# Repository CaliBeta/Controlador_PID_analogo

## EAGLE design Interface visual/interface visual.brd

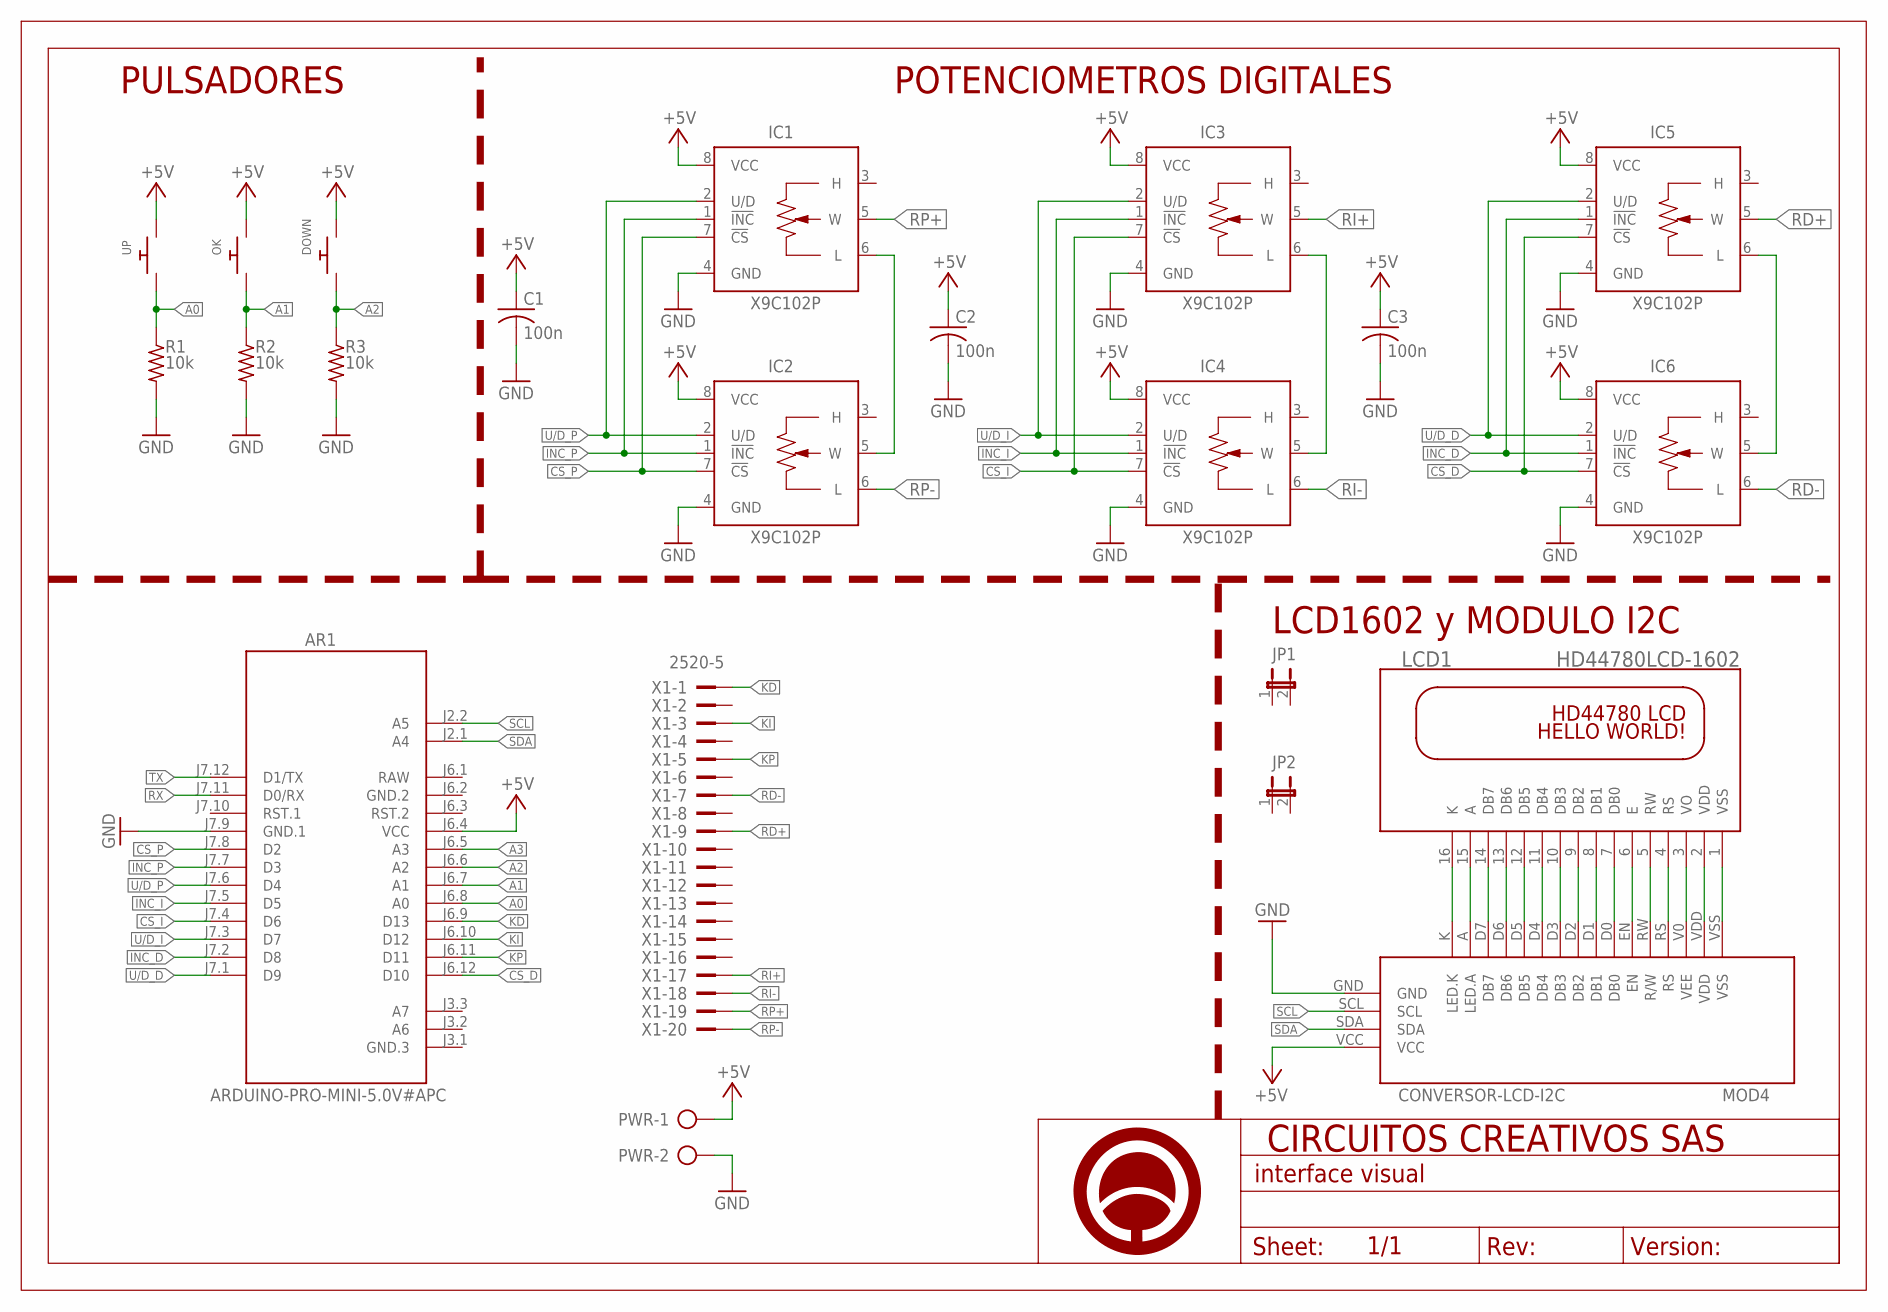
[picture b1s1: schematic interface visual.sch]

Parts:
AR1: ARDUINO-PRO-MINI-5.0V#APC; ARDUINO-PRO-MINI#APC
C1, C2, C3: 100n; C025-025X050
DOWN: SWITCH_PUSHBUTTONEVQ-PE; TACT_PANA-EVQ
IC1, IC2, IC3, IC4, IC5, IC6: X9C102P; DIL08
JP1, JP2: JP1E; JP1
LCD1: HD44780LCD-1602; LCD1602
MOD4: CONVERSOR-LCD-I2C
OK: SWITCH_PUSHBUTTONEVQ-PE; TACT_PANA-EVQ
PWR: AK500/2
R1, R2, R3: 10k; 0204/7
U$1: A4_HORIZONTAL; LOGO
UP: SWITCH_PUSHBUTTONEVQ-PE; TACT_PANA-EVQ
X1: 2520-5; PAK100/2500-5-20

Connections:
+5V: AR1.J6.4 (VCC), C1.1, C2.1, C3.1, DOWN.P$2, IC1.8 (VCC), IC2.8 (VCC), IC3.8 (VCC), IC4.8 (VCC), IC5.8 (VCC), IC6.8 (VCC), MOD4.VCC, OK.P$2, PWR.1, UP.P$2
A0: AR1.J6.8 (A0), R1.1, UP.P$1
A1: AR1.J6.7 (A1), OK.P$1, R2.1
A2: AR1.J6.6 (A2), DOWN.P$1, R3.1
A3: AR1.J6.5 (A3)
CS_D: AR1.J6.12 (D10), IC5.7 (!CS), IC6.7 (!CS)
CS_I: AR1.J7.4 (D6), IC3.7 (!CS), IC4.7 (!CS)
CS_P: AR1.J7.8 (D2), IC1.7 (!CS), IC2.7 (!CS)
GND: AR1.J7.9 (GND.1), C1.2, C2.2, C3.2, IC1.4 (GND), IC2.4 (GND), IC3.4 (GND), IC4.4 (GND), IC5.4 (GND), IC6.4 (GND), MOD4.GND, PWR.2, R1.2, R2.2, R3.2
GND.2: AR1.J6.2 (GND.2)
INC_D: AR1.J7.2 (D8), IC5.1 (!INC), IC6.1 (!INC)
INC_I: AR1.J7.5 (D5), IC3.1 (!INC), IC4.1 (!INC)
INC_P: AR1.J7.7 (D3), IC1.1 (!INC), IC2.1 (!INC)
KD: AR1.J6.9 (D13), X1.1
KI: AR1.J6.10 (D12), X1.3
KP: AR1.J6.11 (D11), X1.5
unnamed: IC3.6 (L), IC4.5 (W)
unnamed: IC1.6 (L), IC2.5 (W)
unnamed: IC5.6 (L), IC6.5 (W)
unnamed: LCD1.3 (VO), MOD4.V0 (VEE)
unnamed: LCD1.4 (RS), MOD4.RS
unnamed: LCD1.5 (RW), MOD4.RW (R/W)
unnamed: LCD1.7 (DB0), MOD4.D0 (DB0)
unnamed: LCD1.6 (E), MOD4.EN
unnamed: LCD1.8 (DB1), MOD4.D1 (DB1)
unnamed: LCD1.9 (DB2), MOD4.D2 (DB2)
unnamed: LCD1.10 (DB3), MOD4.D3 (DB3)
unnamed: LCD1.11 (DB4), MOD4.D4 (DB4)
unnamed: LCD1.12 (DB5), MOD4.D5 (DB5)
unnamed: LCD1.13 (DB6), MOD4.D6 (DB6)
unnamed: LCD1.14 (DB7), MOD4.D7 (DB7)
unnamed: LCD1.15 (A), MOD4.A (LED.A)
unnamed: LCD1.16 (K), MOD4.K (LED.K)
RAW: AR1.J6.1 (RAW)
RD+: IC5.5 (W), X1.9
RD-: IC6.6 (L), X1.7
RI+: IC3.5 (W), X1.17
RI-: IC4.6 (L), X1.18
RP+: IC1.5 (W), X1.19
RP-: IC2.6 (L), X1.20
RX: AR1.J7.11 (D0/RX)
SCL: AR1.J2.2 (A5), MOD4.SCL
SDA: AR1.J2.1 (A4), MOD4.SDA
TX: AR1.J7.12 (D1/TX)
U/D_D: AR1.J7.1 (D9), IC5.2 (U/D), IC6.2 (U/D)
U/D_I: AR1.J7.3 (D7), IC3.2 (U/D), IC4.2 (U/D)
U/D_P: AR1.J7.6 (D4), IC1.2 (U/D), IC2.2 (U/D)
VDD: LCD1.2 (VDD), MOD4.VDD
VSS: LCD1.1 (VSS), MOD4.VSS

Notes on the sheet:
LCD1602 y MODULO I2C
POTENCIOMETROS DIGITALES
PULSADORES

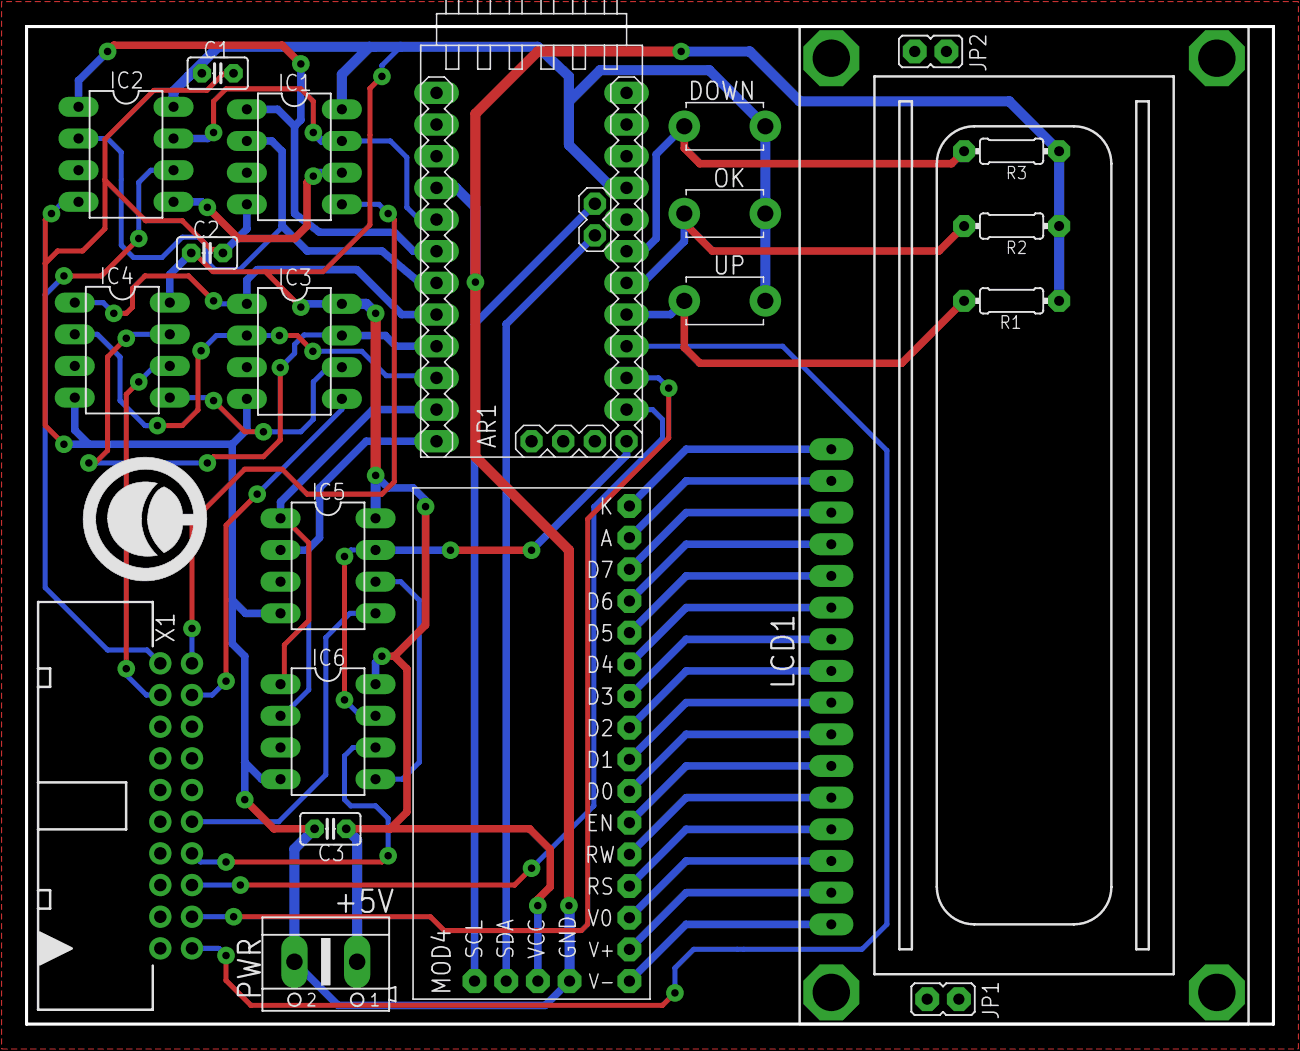
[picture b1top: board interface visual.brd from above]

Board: 2 copper layers, 100.0 x 80.0 mm, 23 parts (0 on the bottom side), 44 nets.

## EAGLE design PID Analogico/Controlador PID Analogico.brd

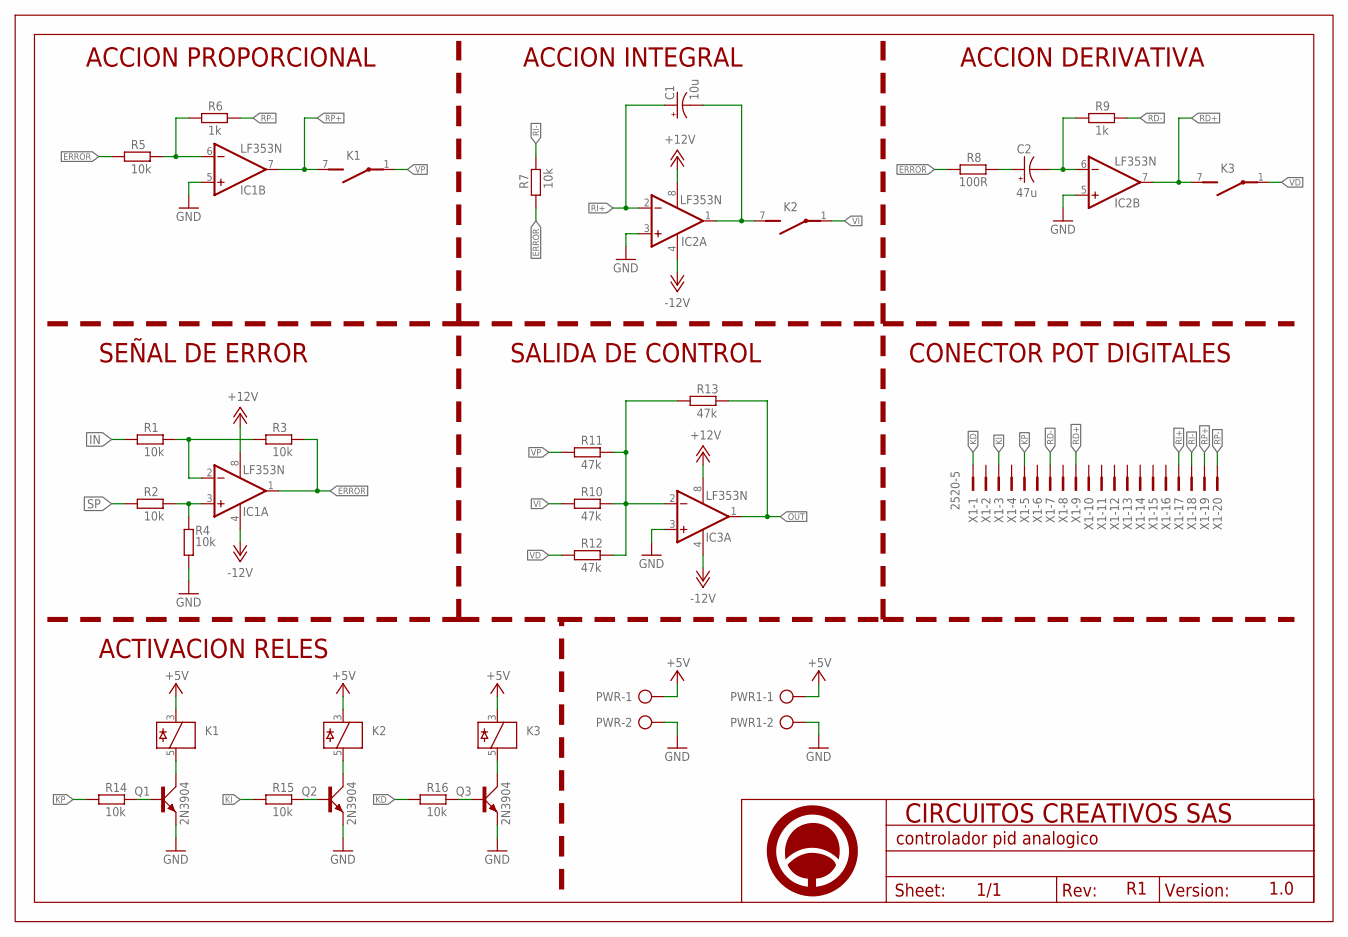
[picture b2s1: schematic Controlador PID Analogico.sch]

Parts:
C1: 10u; E2,5-6E
C2: 47u; E2,5-6E
IC1, IC2, IC3: LF353N; DIL08
K1, K2, K3: 35701331; REED
PWR, PWR1: AK500/2
Q1, Q2, Q3: 2N3904; TO92D
R1, R2, R3, R4, R5, R7, R14, R15, R16: 10k; 0204/7
R6, R9: 1k; 0204/7
R8: 100R; 0204/7
R10, R11, R12, R13: 47k; 0204/7
U$1: A4_HORIZONTAL; LOGO
X1: 2520-5; PAK100/2500-5-20

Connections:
+5V: K1.3, K2.3, K3.3, PWR.1, PWR1.1
+12V: IC1.8 (V+), IC2.8 (V+), IC3.8 (V+)
-12V: IC1.4 (V-), IC2.4 (V-), IC3.4 (V-)
ERROR: IC1.1 (OUT), R3.2, R5.2, R7.2, R8.1
GND: IC1.5 (+IN), IC2.3 (+IN), IC2.5 (+IN), IC3.3 (+IN), PWR.2, PWR1.2, Q1.E, Q2.E, Q3.E, R4.2
IN: R1.1
KD: R16.1, X1.1
KI: R15.1, X1.3
KP: R14.1, X1.5
unnamed: IC1.2 (-IN), R1.2, R3.1
unnamed: IC1.3 (+IN), R2.2, R4.1
unnamed: IC1.6 (-IN), R5.1, R6.1
unnamed: C1.-, IC2.1 (OUT), K2.7 (S)
unnamed: C2.-, IC2.6 (-IN), R9.1
unnamed: C2.+, R8.2
unnamed: IC3.2 (-IN), R10.2, R11.2, R12.2, R13.1
unnamed: Q1.B, R14.2
unnamed: K1.5, Q1.C
unnamed: Q2.B, R15.2
unnamed: K2.5, Q2.C
unnamed: Q3.B, R16.2
unnamed: K3.5, Q3.C
OUT: IC3.1 (OUT), R13.2
RD+: IC2.7 (OUT), K3.7 (S), X1.9
RD-: R9.2, X1.7
RI+: C1.+, IC2.2 (-IN), X1.17
RI-: R7.1, X1.18
RP+: IC1.7 (OUT), K1.7 (S), X1.19
RP-: R6.2, X1.20
SP: R2.1
VD: K3.1, R12.1
VI: K2.1, R10.1
VP: K1.1, R11.1

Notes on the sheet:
1.0
ACCION PROPORCIONAL
ACCION INTEGRAL
ACCION DERIVATIVA
SEÑAL DE ERROR
SALIDA DE CONTROL
ACTIVACION RELES
CONECTOR POT DIGITALES

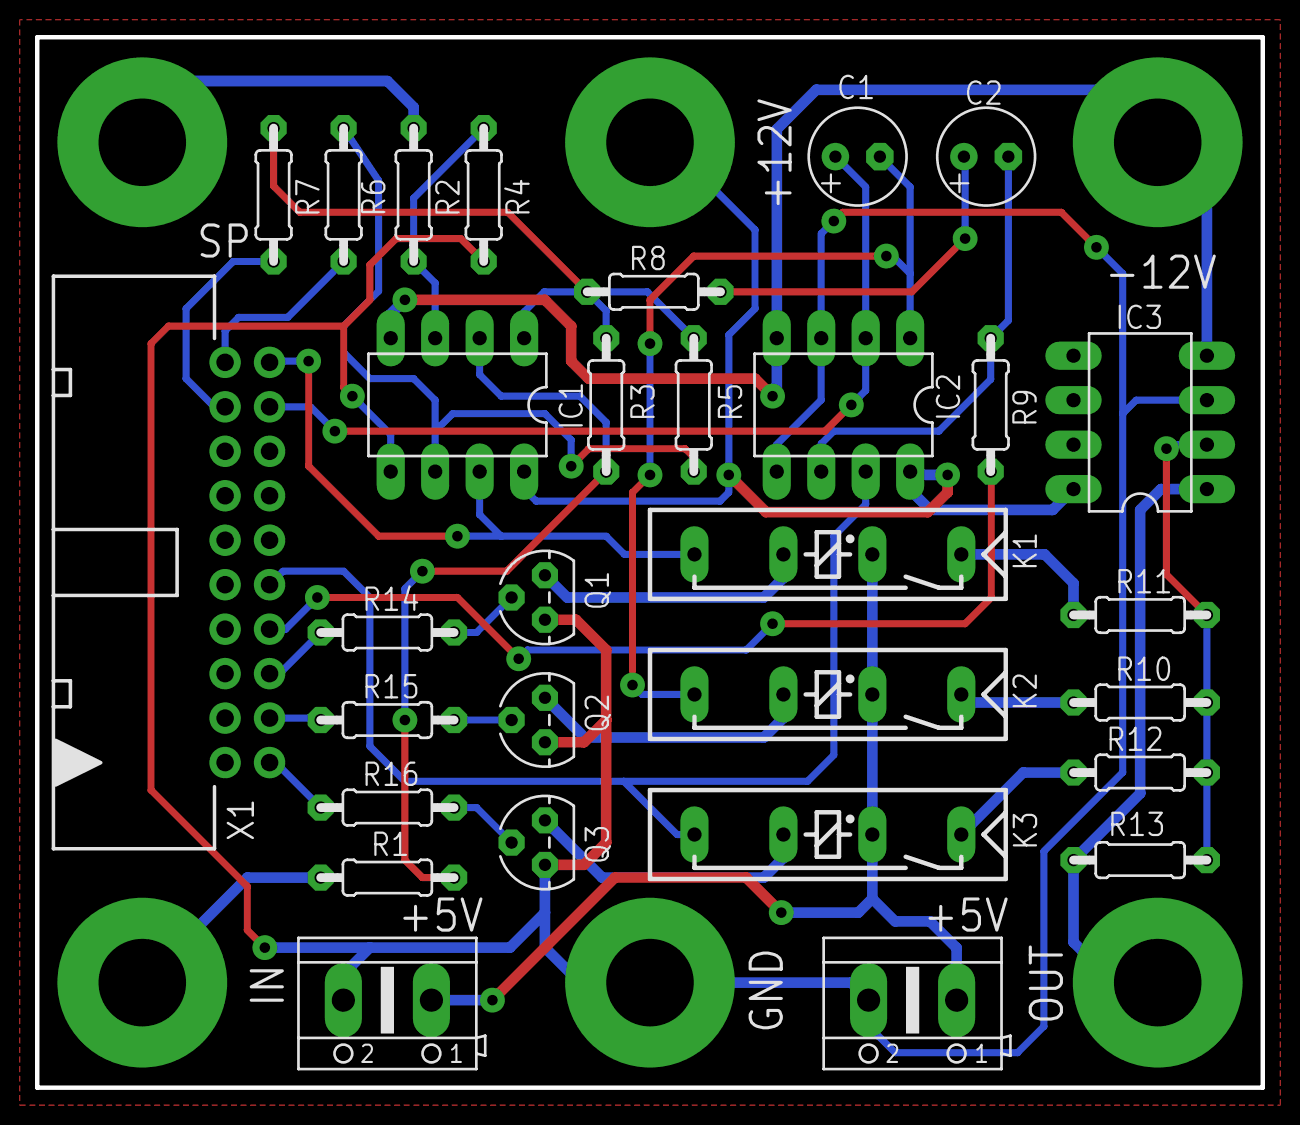
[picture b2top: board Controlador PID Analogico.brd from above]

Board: 2 copper layers, 70.0 x 60.0 mm, 31 parts (1 on the bottom side), 31 nets.

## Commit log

2017-09-19 Commit inicial. Comienzo del SCH
2018-09-10 Terminado etapa restador y las tres acciones de control
2019-01-15 Terminado SCH y BRD. generando los Gerber
2019-01-15 Agregado SCH interface visual
2019-01-15 Agregado BRD interface visual
2019-01-15 Generado imagenes del SCH y BRD interface visual
2019-01-15 Generado Gerber interface visual
2019-01-15 Agregado Firmware para la interface visual

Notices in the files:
parts and their libraries:
DIY- comercial modules: Released under the Creative Commons Attribution 4.0 International License: http://creativecommons.org/licenses/by/4.0
